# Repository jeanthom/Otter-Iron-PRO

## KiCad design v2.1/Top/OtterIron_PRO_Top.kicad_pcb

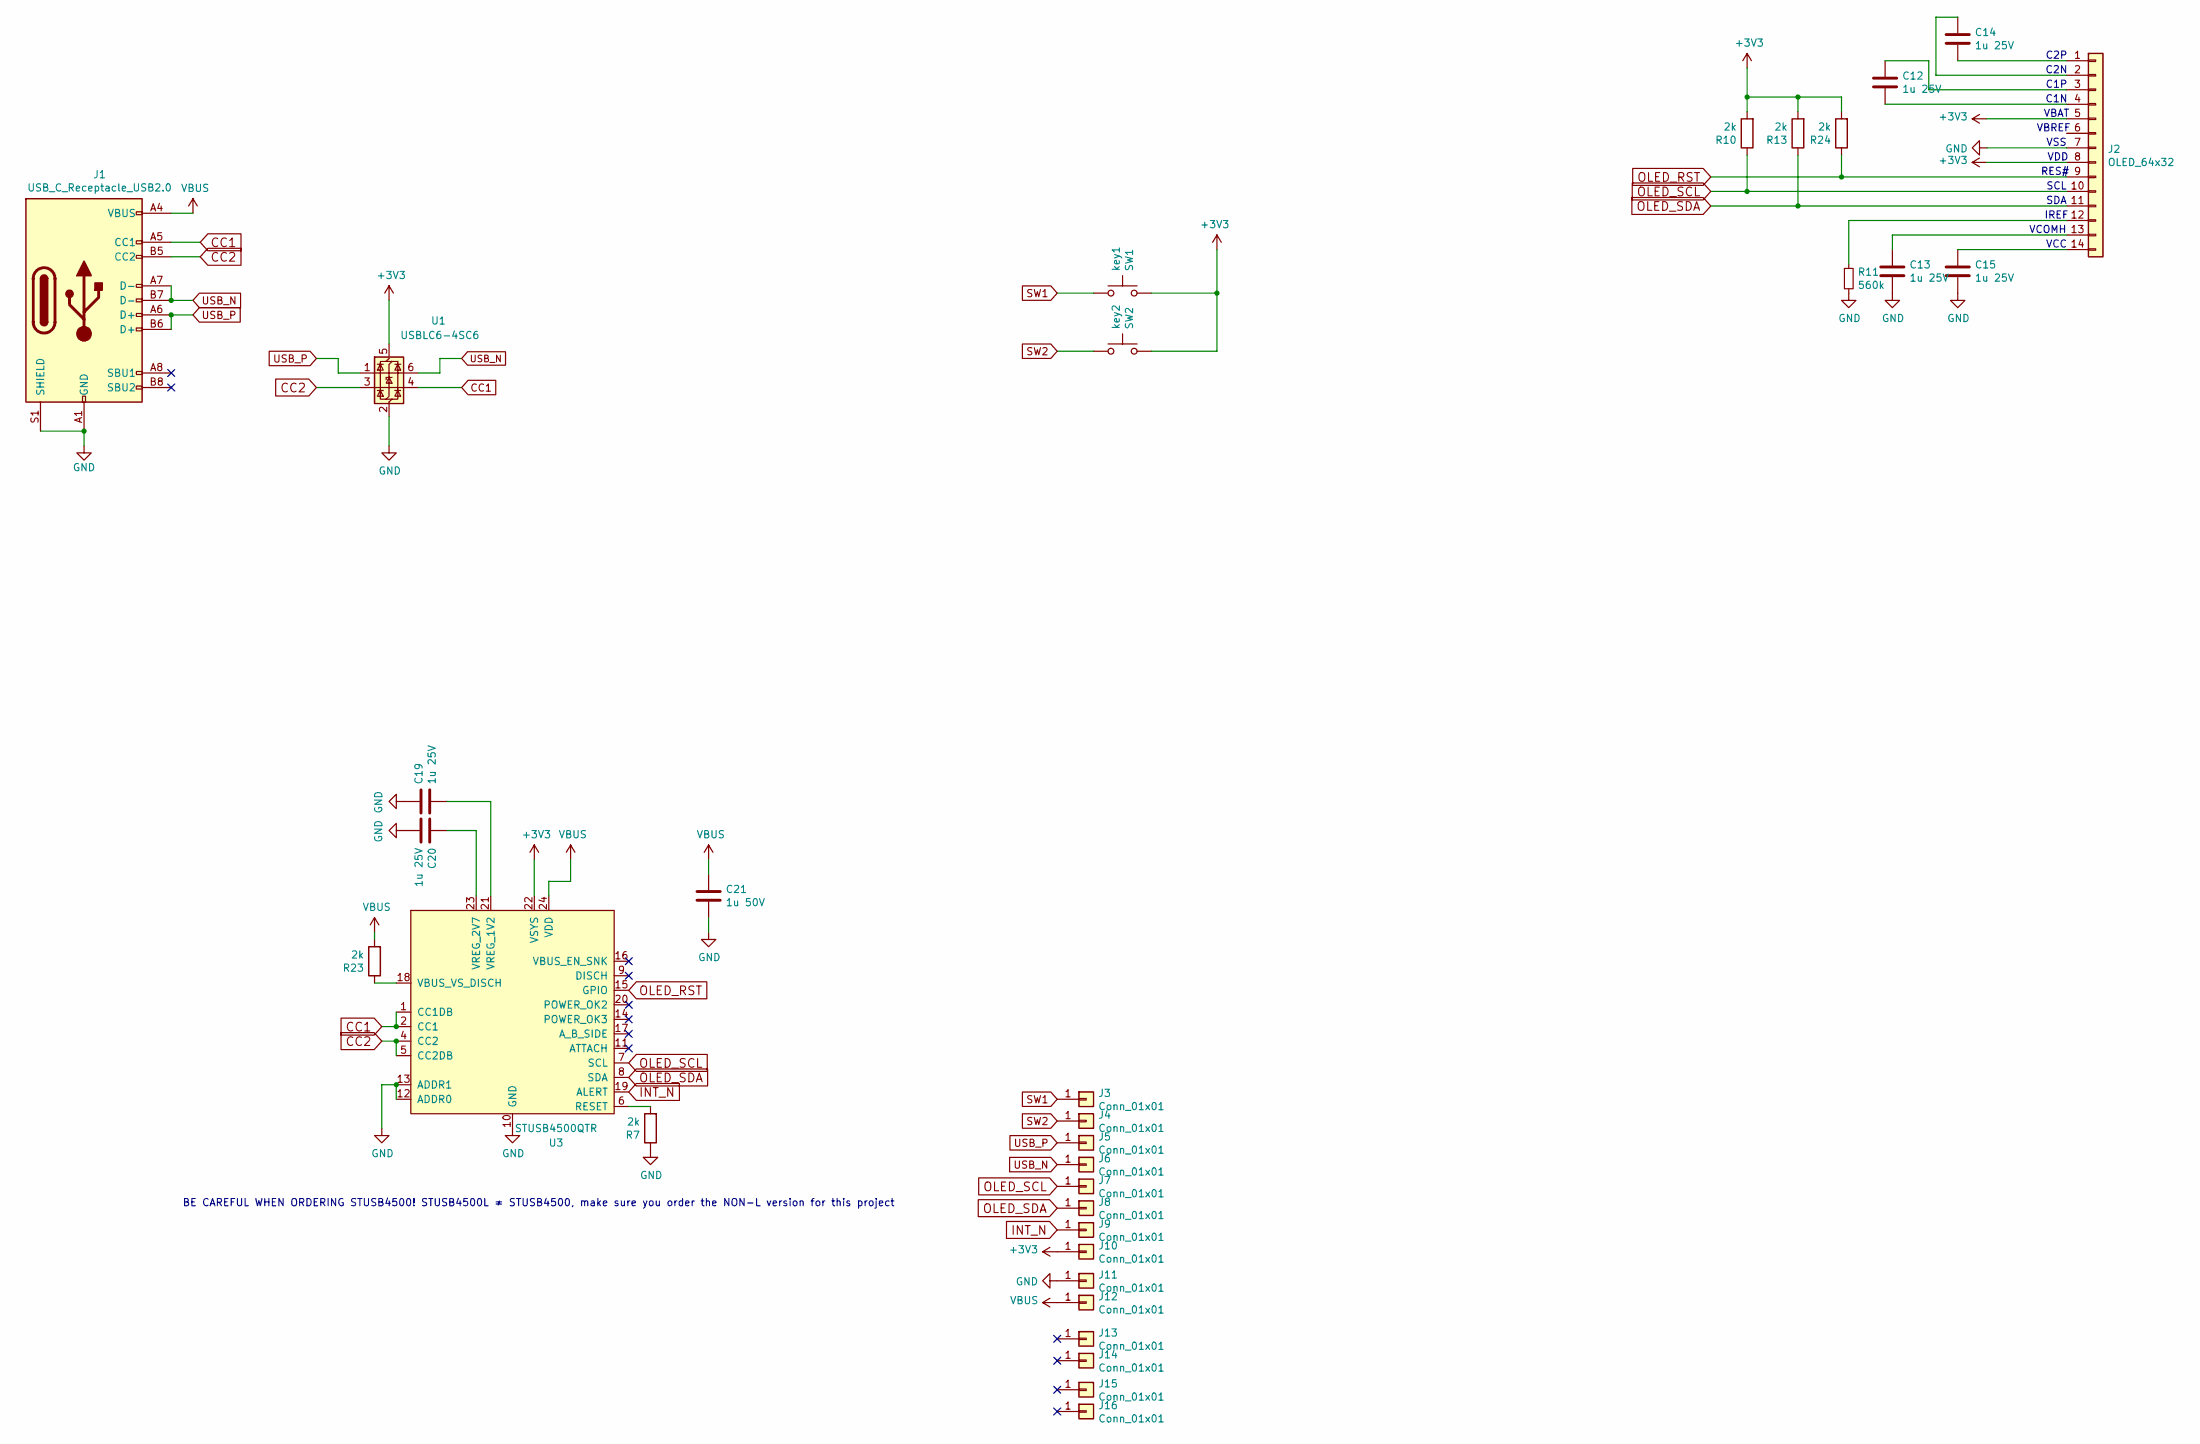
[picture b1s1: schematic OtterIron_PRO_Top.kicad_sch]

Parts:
C12, C13, C14, C15, C19, C20: 1u 25V; C_0603; LCSC C15849
C21: 1u 50V; C_0603; LCSC C15849
J1: USB_C_Receptacle_USB2.0; USB-C 16Pin; LCSC C167321
J2: OLED_64x32; 0.69OLED
J3, J4, J7, J8, J9, J10: Conn_01x01; pad_1_2
J5, J6: Conn_01x01; pad_0.75_3
J11, J12, J13, J14, J15, J16: Conn_01x01; pad_1.5_3
R7, R10, R13, R23, R24: 2k; R_0603; LCSC C4109
R11: 560k; R_0603; LCSC C23203
SW1: key1; SW_SPST_EVQP7C; LCSC C388883
SW2: key2; SW_SPST_EVQP7C; LCSC C388883
U1: USBLC6-4SC6; SOT-23-6; LCSC C7519
U3: STUSB4500QTR; QFN-24-1EP_4x4mm_P0.5mm_EP2.7x2.7mm; LCSC C2678061

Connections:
+3V3: J2.5, J2.8, J10.1, R10.2, R13.2, R24.2, SW1.1, SW2.1, U1.5 (VBUS), U3.22 (VSYS)
CC1: J1.A5 (CC1), U1.4 (I/O2), U3.1 (CC1DB), U3.2 (CC1)
CC2: J1.B5 (CC2), U1.3 (I/O2), U3.4 (CC2), U3.5 (CC2DB)
GND: C13.2, C15.2, C19.1, C20.2, C21.2, J1.A1 (GND), J1.A12 (GND), J1.B1 (GND), J1.B12 (GND), J1.S1 (SHIELD), J2.7, J11.1, R7.1, R11.2, U1.2 (GND), U3.10 (GND), U3.12 (ADDR0), U3.13 (ADDR1), U3.25 (GND)
INT_N: J9.1, U3.19 (ALERT)
unnamed: C14.2, J2.1
unnamed: C14.1, J2.2
unnamed: C12.1, J2.3
unnamed: C12.2, J2.4
unnamed: J2.12, R11.1
unnamed: C13.1, J2.13
unnamed: C15.1, J2.14
unnamed: R7.2, U3.6 (RESET)
unnamed: R23.1, U3.18 (VBUS_VS_DISCH)
unnamed: C19.2, U3.21 (VREG_1V2)
unnamed: C20.1, U3.23 (VREG_2V7)
OLED_RST: J2.9, R24.1, U3.15 (GPIO)
OLED_SCL: J2.10, J7.1, R10.1, U3.7 (SCL)
OLED_SDA: J2.11, J8.1, R13.1, U3.8 (SDA)
SW1: J3.1, SW1.2
SW2: J4.1, SW2.2
USB_N: J1.A7 (D-), J1.B7 (D-), J6.1, U1.6 (I/O1)
USB_P: J1.A6 (D+), J1.B6 (D+), J5.1, U1.1 (I/O1)
VBUS: C21.1, J1.A4 (VBUS), J1.A9 (VBUS), J1.B4 (VBUS), J1.B9 (VBUS), J12.1, R23.2, U3.24 (VDD)

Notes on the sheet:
VBAT
SCL
RES#
IREF
SDA
VBREF
C2P
C1P
VCC
C1N
C2N
BE CAREFUL WHEN ORDERING STUSB4500! STUSB4500L ≠ STUSB4500, make sure you order the NON-L version for this project
VCOMH
VSS
VDD

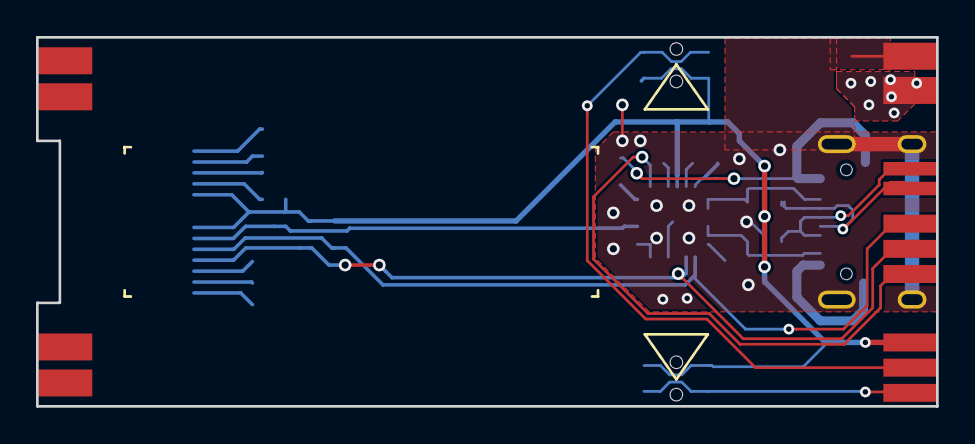
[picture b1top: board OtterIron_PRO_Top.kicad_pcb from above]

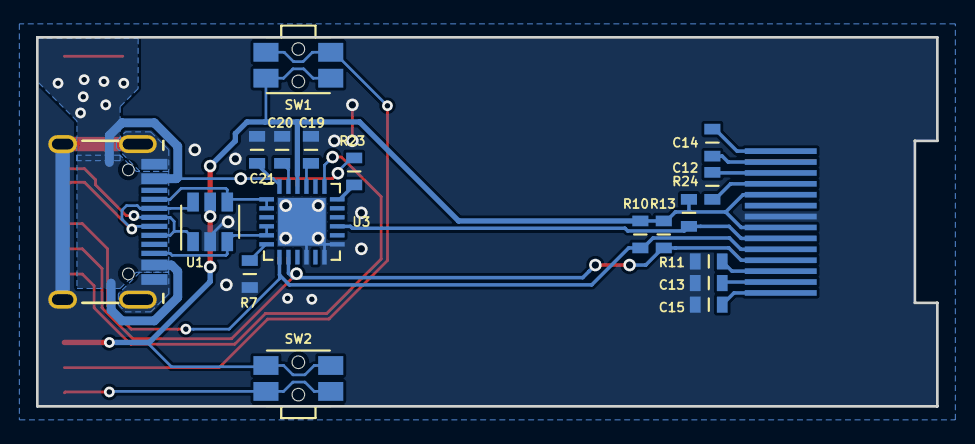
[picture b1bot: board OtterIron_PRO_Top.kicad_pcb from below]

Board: 2 copper layers, 50.0 x 20.5 mm, 33 parts (19 on the bottom side), 24 nets.

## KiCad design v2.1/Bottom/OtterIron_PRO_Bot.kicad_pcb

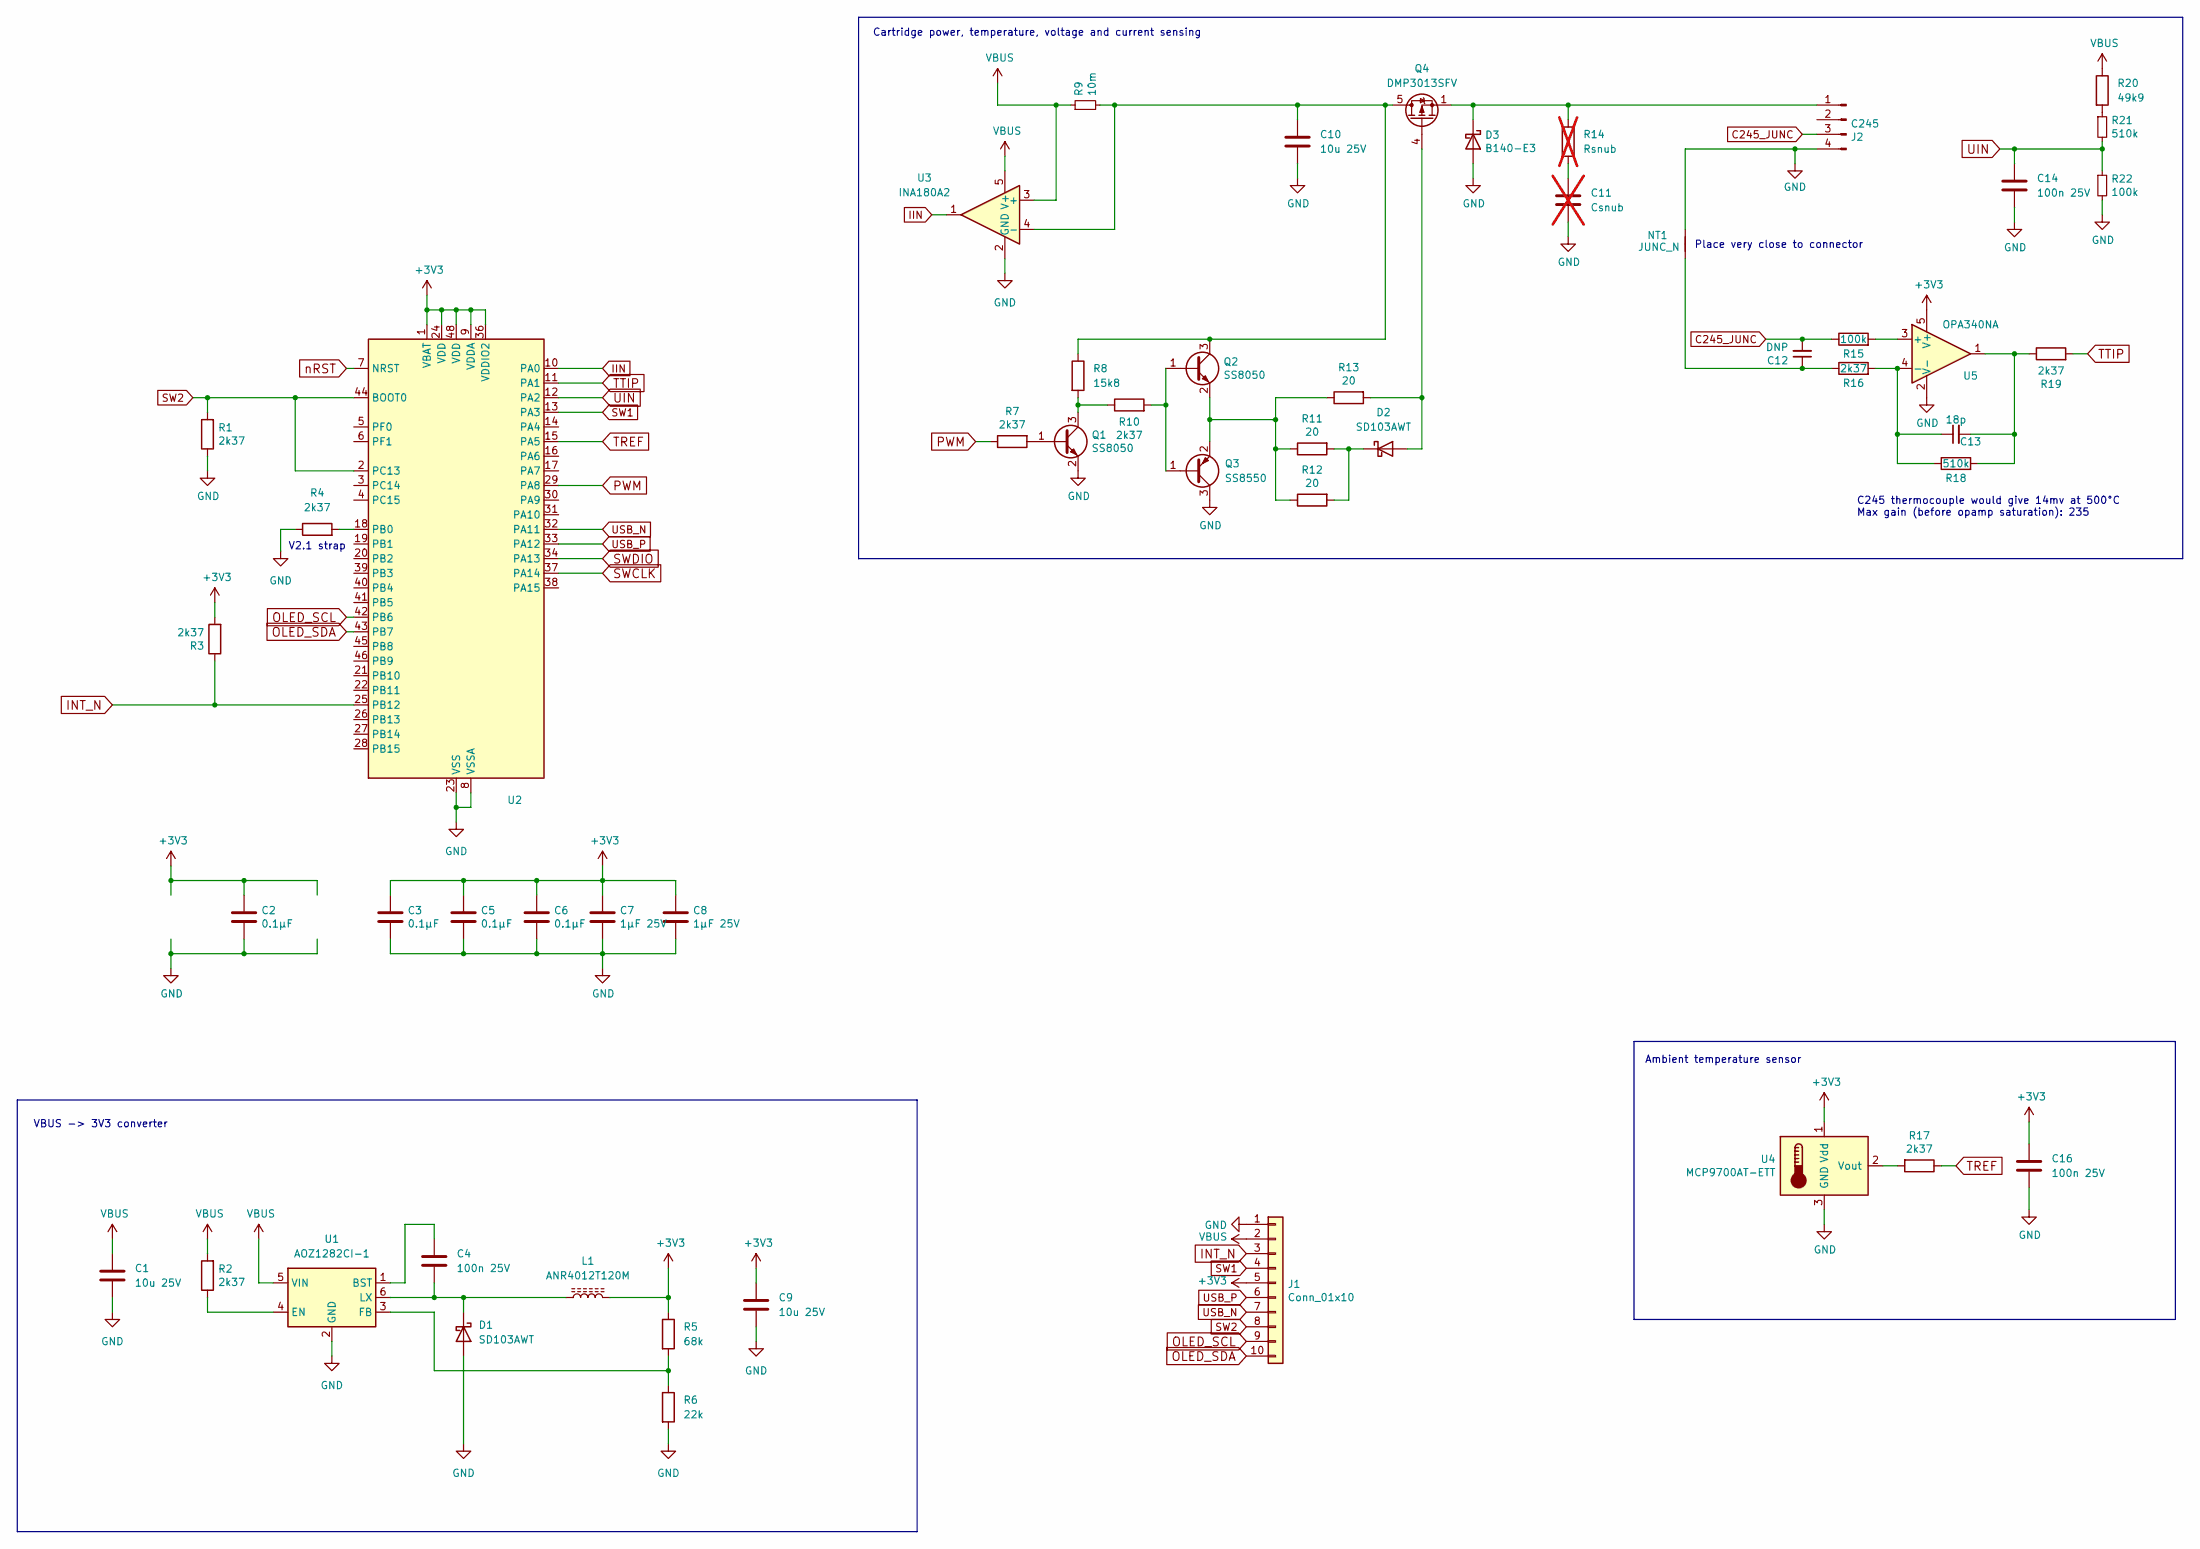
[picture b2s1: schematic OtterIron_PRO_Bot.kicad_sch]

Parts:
C1, C9, C10: 10u 25V; C_0603_1608Metric; LCSC C96446
C2, C3, C5, C6: 0.1μF; C_0402_1005Metric
C4, C14, C16: 100n 25V; C_0402_1005Metric; LCSC C100072
C7, C8: 1μF 25V; C_0603_1608Metric
C11: Csnub; C_0603_1608Metric; not fitted
C12: DNP; C_0402_1005Metric
C13: 18p; C_0402_1005Metric
D1, D2: SD103AWT; D_SOD-523; LCSC C22466357
D3: B140-E3; D_SOD-123F
J1: Conn_01x10; PinHeader_1x10_P2.00mm_Horizontal
J2: C245; PinHeader_1x04_P2.54mm_Horizontal
L1: ANR4012T120M; L_APV_ANR4012; LCSC C6808080
NT1: JUNC_N; NetTie-2_SMD_Pad0.5mm
Q1, Q2: SS8050; SOT-23
Q3: SS8550; SOT-23
Q4: DMP3013SFV; Diodes_PowerDI3333-8; LCSC C264098
R1, R2, R3, R4, R7, R10, R16, R17, R19: 2k37; R_0402_1005Metric
R5: 68k; R_0402_1005Metric; LCSC C137969
R6: 22k; R_0402_1005Metric; LCSC C852544
R8: 15k8; R_0402_1005Metric; LCSC C852544
R9: 10m; R_0805_2012Metric; LCSC C270927
R11, R12, R13: 20; R_0402_1005Metric
R14: Rsnub; R_0402_1005Metric; not fitted
R15, R22: 100k; R_0402_1005Metric
R18, R21: 510k; R_0402_1005Metric; LCSC C11616
R20: 49k9; R_0402_1005Metric; LCSC C137969
U1: AOZ1282CI-1; SOT-23-6; LCSC C2070766
U2: STM32F072C8Tx; LQFP-48_7x7mm_P0.5mm
U3: INA180A2; SOT-23-5
U4: MCP9700AT-ETT; SOT-23
U5: OPA340NA; SOT-23-5

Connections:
+3V3: C2.1, C3.1, C5.1, C6.1, C7.1, C8.1, C9.1, C16.1, J1.5, L1.2, R3.2, R5.1, U2.1 (VBAT), U2.9 (VDDA), U2.24 (VDD), U2.36 (VDDIO2), U2.48 (VDD), U4.1 (Vdd), U5.5 (V+)
C245_JUNC: C12.2, J2.3, R15.1
GND: C1.2, C2.2, C3.2, C5.2, C6.2, C7.2, C8.2, C9.2, C10.2, C11.2, C14.2, C16.2, D1.2 (A), D3.2 (A), J1.1, J2.4, NT1.2, Q1.2 (E), Q3.3 (C), R1.1, R4.1, R6.2, R22.2, U1.2 (GND), U2.8 (VSSA), U2.23 (VSS), U2.35 (VSS), U2.47 (VSS), U3.2 (GND), U4.3 (GND), U5.2 (V-)
IIN: U2.10 (PA0), U3.1
INT_N: J1.3, R3.1, U2.25 (PB12)
unnamed: C11.1, R14.2
unnamed: C12.1, NT1.1, R16.1
unnamed: C13.2, R18.2, R19.1, U5.1
unnamed: C4.2, D1.1 (K), L1.1, U1.6 (LX)
unnamed: D2.2 (A), Q4.4 (G), R13.2
unnamed: D2.1 (K), R11.2, R12.2
unnamed: D3.1 (K), J2.1, Q4.1 (S), Q4.2 (S), Q4.3 (S), R14.1
unnamed: Q1.1 (B), R7.2
unnamed: Q1.3 (C), R8.2, R10.1
unnamed: Q2.1 (B), Q3.1 (B), R10.2
unnamed: C10.1, Q2.3 (C), Q4.5 (D), R8.1, R9.2, U3.4 (-)
unnamed: Q2.2 (E), Q3.2 (E), R11.1, R12.1, R13.1
unnamed: R20.2, R21.1
unnamed: C4.1, U1.1 (BST)
unnamed: R2.1, U1.4 (EN)
unnamed: R5.2, R6.1, U1.3 (FB)
unnamed: R4.2, U2.18 (PB0)
unnamed: R17.2, U4.2 (Vout)
unnamed: R15.2, U5.3 (+)
unnamed: C13.1, R16.2, R18.1, U5.4 (-)
OLED_SCL: J1.9, U2.42 (PB6)
OLED_SDA: J1.10, U2.43 (PB7)
PWM: R7.1, U2.29 (PA8)
SW1: J1.4, U2.13 (PA3)
SW2: J1.8, R1.2, U2.2 (PC13), U2.44 (BOOT0)
SWCLK: U2.37 (PA14)
SWDIO: U2.34 (PA13)
TREF: R17.1, U2.15 (PA5)
TTIP: R19.2, U2.11 (PA1)
UIN: C14.1, R21.2, R22.1, U2.12 (PA2)
USB_N: J1.7, U2.32 (PA11)
USB_P: J1.6, U2.33 (PA12)
VBUS: C1.1, J1.2, R2.2, R9.1, R20.1, U1.5 (VIN), U3.3 (+), U3.5 (V+)
nRST: U2.7 (NRST)

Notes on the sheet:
Place very close to connector
Cartridge power, temperature, voltage and current sensing
V2.1 strap
VBUS -> 3V3 converter
Ambient temperature sensor
C245 thermocouple would give 14mv at 500°C Max gain (before opamp saturation): 235

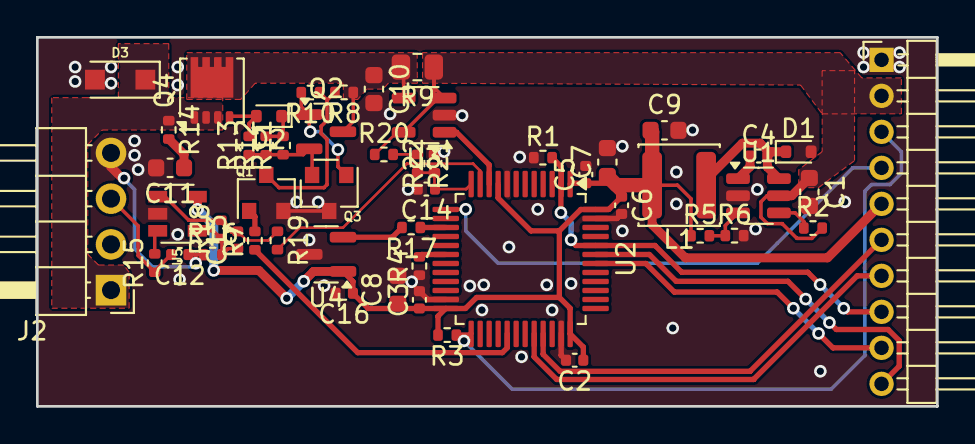
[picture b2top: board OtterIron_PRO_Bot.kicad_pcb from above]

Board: 2 copper layers, 50.0 x 20.5 mm, 53 parts (0 on the bottom side), 36 nets.

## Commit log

2025-04-08 Add v2.1
    Project files were updated to Kicad 9.
    Top PCB:
    - Use 2k resistors (easier to source)
    - Use 1u capacitors everywhere
    - Connect OLED reset line to STUSB4500 GPIO
    - Add LCSC part numbers
